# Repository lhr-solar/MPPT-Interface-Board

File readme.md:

# MPPT-Interface-Board
Author: Ravi Shah  
This Power and CAN interface board for the TPPE SEC-B175-7A Maximum Power Point Tracker provides an interface allowing them to connect to fuse box power and CarCAN. Since CarCAN on Daybreak operates at 5V, a 12V (fusebox) to 9V isolated buck converter is used to meet the minimum 6V requirement of the MPPTs.
## BOM
Mouser Cart: https://www.mouser.com/ProjectManager/ProjectDetail.aspx?AccessID=ef21a76273  
IBOM: BOM/ibom.html (open and view in browser)
## Connectors
| # | Name | Type | Ideal Voltage |
| - | - | - | - |
| J1  | FIRST MPPT | Micro-Fit_3.0_43045-0612_2x03_P3.00mm_Vertical Female | +9V |
| J2  | LAST MPPT | Micro-Fit_3.0_43045-0612_2x03_P3.00mm_Vertical Female | +9V |
| J3  | CarCAN IN | Micro-Fit_3.0_43650-0415_1x04_P3.00mm_Vertical Female | +5V |
| J4  | CarCAN OUT | Micro-Fit_3.0_43650-0415_1x04_P3.00mm_Vertical Female | +5V |
| J5  | FUSEBOX | Micro-Fit_3.0_43650-0215_1x02_P3.00mm_Vertical Female | +12V |
## 3D Model

## PCB

## Schematic

## Application Note
The FIRST MPPT connector is for the first MPPT this board connects to. From there, up to 4 (unverified!) MPPTs can be daisy chained by connecting the output of the first MPPT to the input of the second and so on. The LAST MPPT connector is where the output of the last MPPT in the daisy chain should be connected.

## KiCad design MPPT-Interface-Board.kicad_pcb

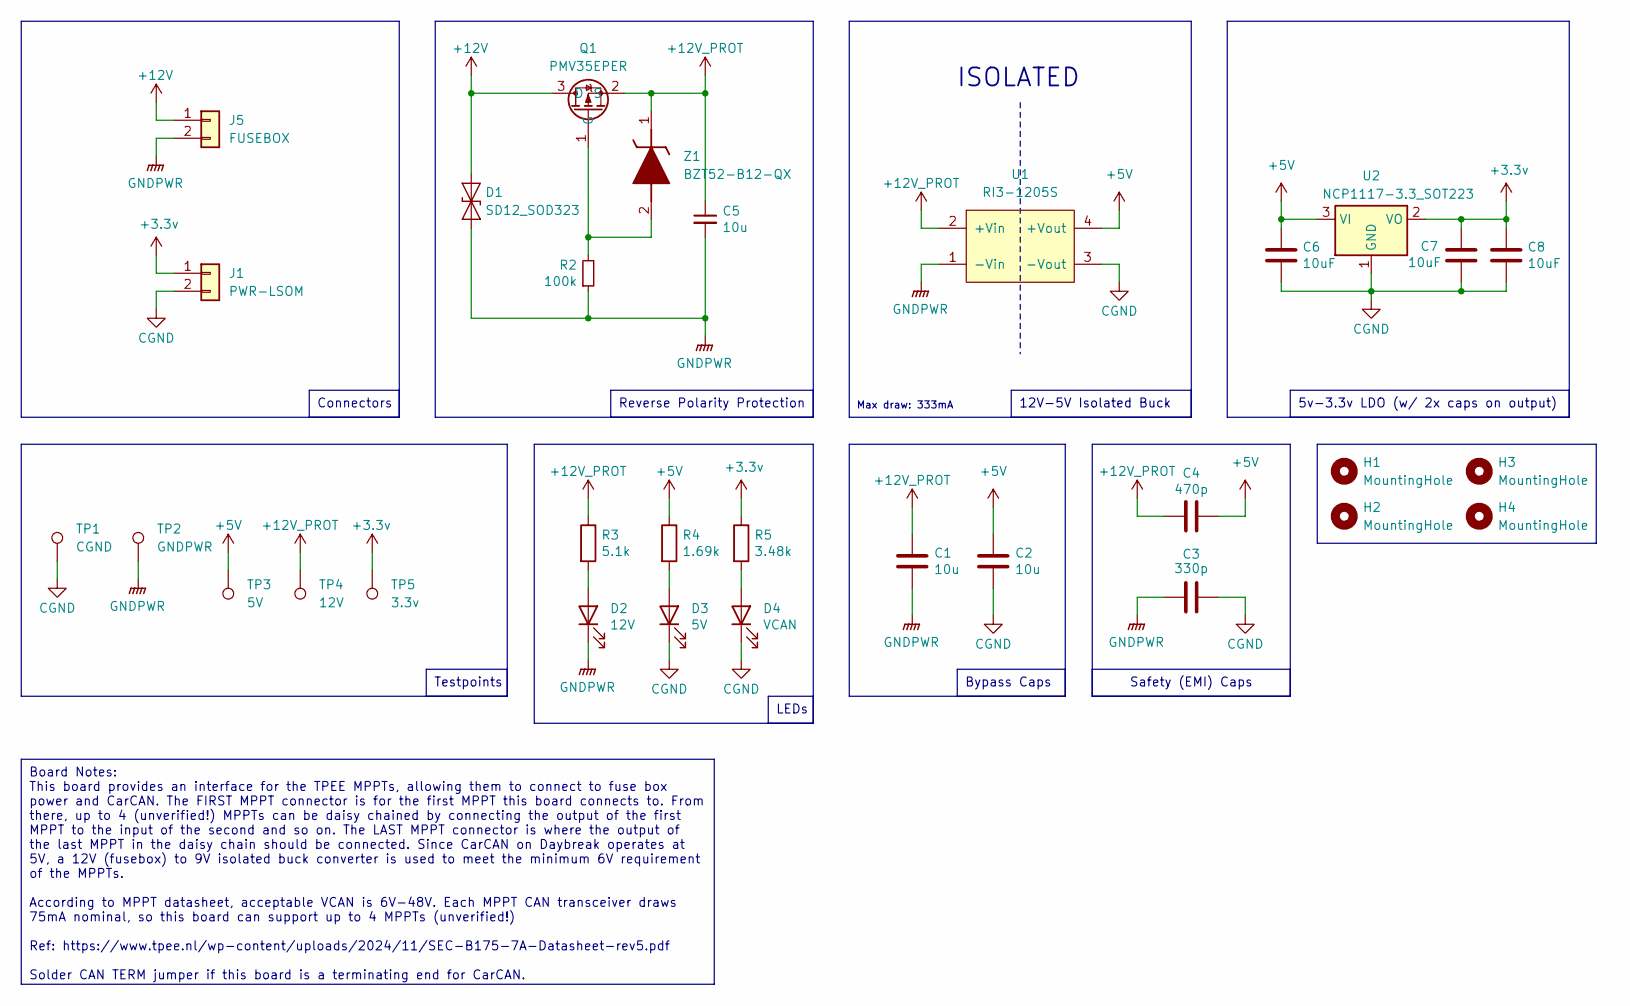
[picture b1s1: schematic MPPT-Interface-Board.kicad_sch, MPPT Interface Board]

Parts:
C1, C2: 10u; C_0805_2012Metric; Mouser Part Number 581-22201C106KAT2A
C3: 330p; C_0805_2012Metric
C4: 470p; C_0805_2012Metric
C5: 10u; C_0805_2012Metric
C6, C7, C8: 10uF; C_0805_2012Metric; Mouser Part Number 963-TMK212BBJ106MGHT
D1: SD12_SOD323; D_SOD-323
D2: 12V; LED_0805_2012Metric; Mouser Part Number 604-APTD2012LCGCK
D3: 5V; LED_0805_2012Metric; Mouser Part Number 604-APTD2012LCGCK
D4: VCAN; LED_0805_2012Metric; Mouser Part Number 604-APTD2012LCGCK
H1, H2, H3, H4: MountingHole; MountingHole_3mm
J1: PWR-LSOM; Molex_Micro-Fit_3.0_43650-0215_1x02_P3.00mm_Vertical
J5: FUSEBOX; Molex_Micro-Fit_3.0_43650-0215_1x02_P3.00mm_Vertical
Q1: PMV35EPER; SOT-23
R2: 100k; R_0805_2012Metric
R3: 5.1k; R_0805_2012Metric; Mouser Part Number 71-CRCW0805-22.1K-E3
R4: 1.69k; R_0805_2012Metric; Mouser Part Number 71-CRCW0805-22.1K-E3
R5: 3.48k; R_0805_2012Metric; Mouser Part Number 71-CRCW0805-22.1K-E3
TP1: CGND; TestPoint_Pad_1.0x1.0mm
TP2: GNDPWR; TestPoint_Pad_1.0x1.0mm
TP3: 5V; TestPoint_Pad_1.0x1.0mm
TP4: 12V; TestPoint_Pad_1.0x1.0mm
TP5: 3.3v; TestPoint_Pad_1.0x1.0mm
U1: RI3-1205S; RI3_DC_Converter; Mouser Part Number 919-RI3-1205S
U2: NCP1117-3.3_SOT223; SOT-223-3_TabPin2; Mouser Part Number 863-NCP1117ST33T3G
Z1: BZT52-B12-QX; BZT52B12QX; Mouser Part Number 771-BZT52-B12-QX

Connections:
+3.3v: C7.1, C8.1, J1.1, R5.1, TP5.1, U2.2 (VO)
+5V: C2.1, C4.2, C6.1, R4.1, TP3.1, U1.4 (+Vout), U2.3 (VI)
+12V: D1.2 (A2), J5.1, Q1.3 (D)
+12V_PROT: C1.1, C4.1, C5.1, Q1.2 (S), R3.1, TP4.1, U1.2 (+Vin), Z1.1 (K)
CGND: C2.2, C3.2, C6.2, C7.2, C8.2, D3.1 (K), D4.1 (K), J1.2, TP1.1, U1.3 (-Vout), U2.1 (GND)
GNDPWR: C1.2, C3.1, C5.2, D1.1 (A1), D2.1 (K), J5.2, R2.1, TP2.1, U1.1 (-Vin)
unnamed: D2.2 (A), R3.2
unnamed: D3.2 (A), R4.2
unnamed: D4.2 (A), R5.2
unnamed: Q1.1 (G), R2.2, Z1.2 (A)

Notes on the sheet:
Board Notes: This board provides an interface for the TPEE MPPTs, allowing them to connect to fuse box power and CarCAN. The FIRST MPPT connector is for the first MPPT this board connects to. From there, up to 4 (unverified!) MPPTs can be daisy chained by connecting the output of the first MPPT to 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
Connectors
Reverse Polarity Protection
Testpoints
LEDs
Safety (EMI) Caps
Bypass Caps
12V-5V Isolated Buck
5v-3.3v LDO (w/ 2x caps on output)
ISOLATED
Max draw: 333mA

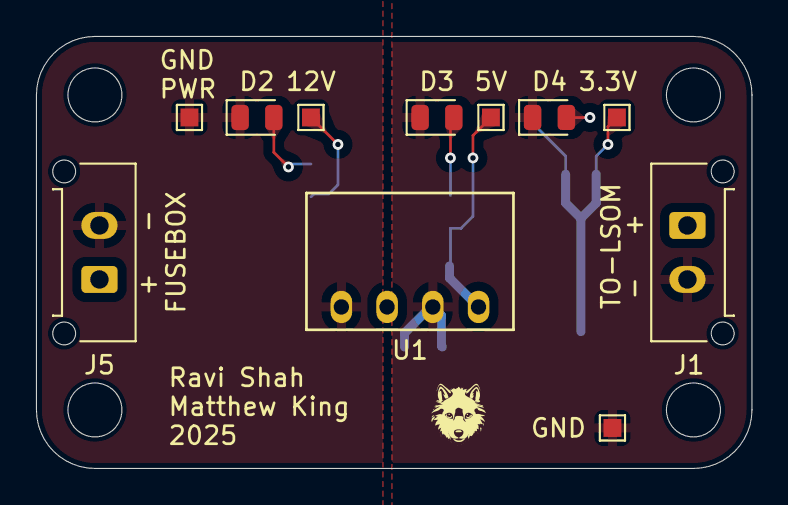
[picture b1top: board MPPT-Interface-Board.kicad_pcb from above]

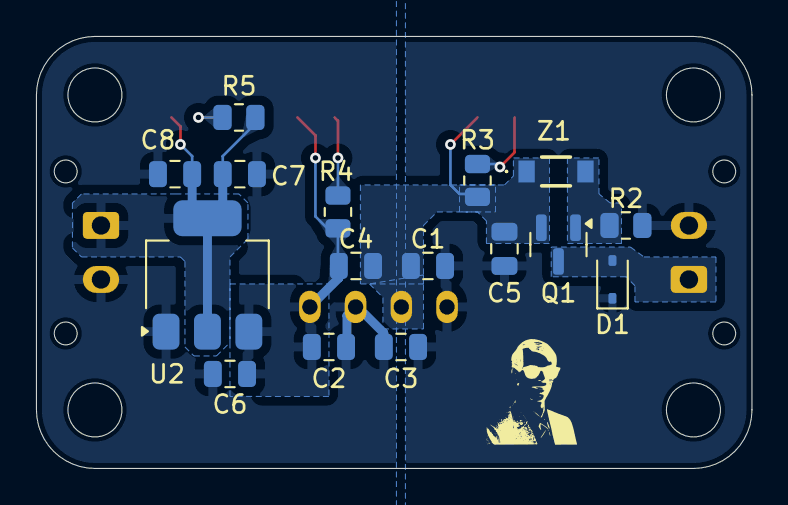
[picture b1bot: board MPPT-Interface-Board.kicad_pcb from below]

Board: 2 copper layers, 39.8 x 24.0 mm, 31 parts (16 on the bottom side), 10 nets.

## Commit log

2025-02-10 readme
2025-02-10 add kicad project
2025-02-10 common libs
2025-02-10 update symbols/footprints from lib
2025-02-15 initial sch
2025-02-15 add candapter conn
2025-02-15 PR template
2025-02-15 add RPP
2025-02-15 fix loop?
2025-02-15 add indicator LEDs
2025-02-15 more fixes
2025-02-15 P/N for everything
2025-02-15 fix bypass cap
2025-02-16 footprints
2025-02-16 uhm so why am i so stupid
2025-02-16 initial layout (unrouted)
2025-02-16 add silk labels
2025-02-16 routed
2025-02-16 change carcan to 4 pin & add start termination
2025-02-17 redo layout/routing/silks
2025-02-17 lil smaller
2025-02-17 3d & BOM
2025-02-17 mouser/ibom
2025-02-17 cant read ig
2025-02-17 make gndpwr larger
2025-02-17 lakshay make board black pls
2025-02-17 fix plane connection
2025-02-17 board notes + readme stuff
2025-02-17 add pcb, sch, 3d to readme
2025-03-04 add connectors table to readme
2025-05-18 Changed up to interface data acq leader
2025-05-19 Smaller version - gerbers made
